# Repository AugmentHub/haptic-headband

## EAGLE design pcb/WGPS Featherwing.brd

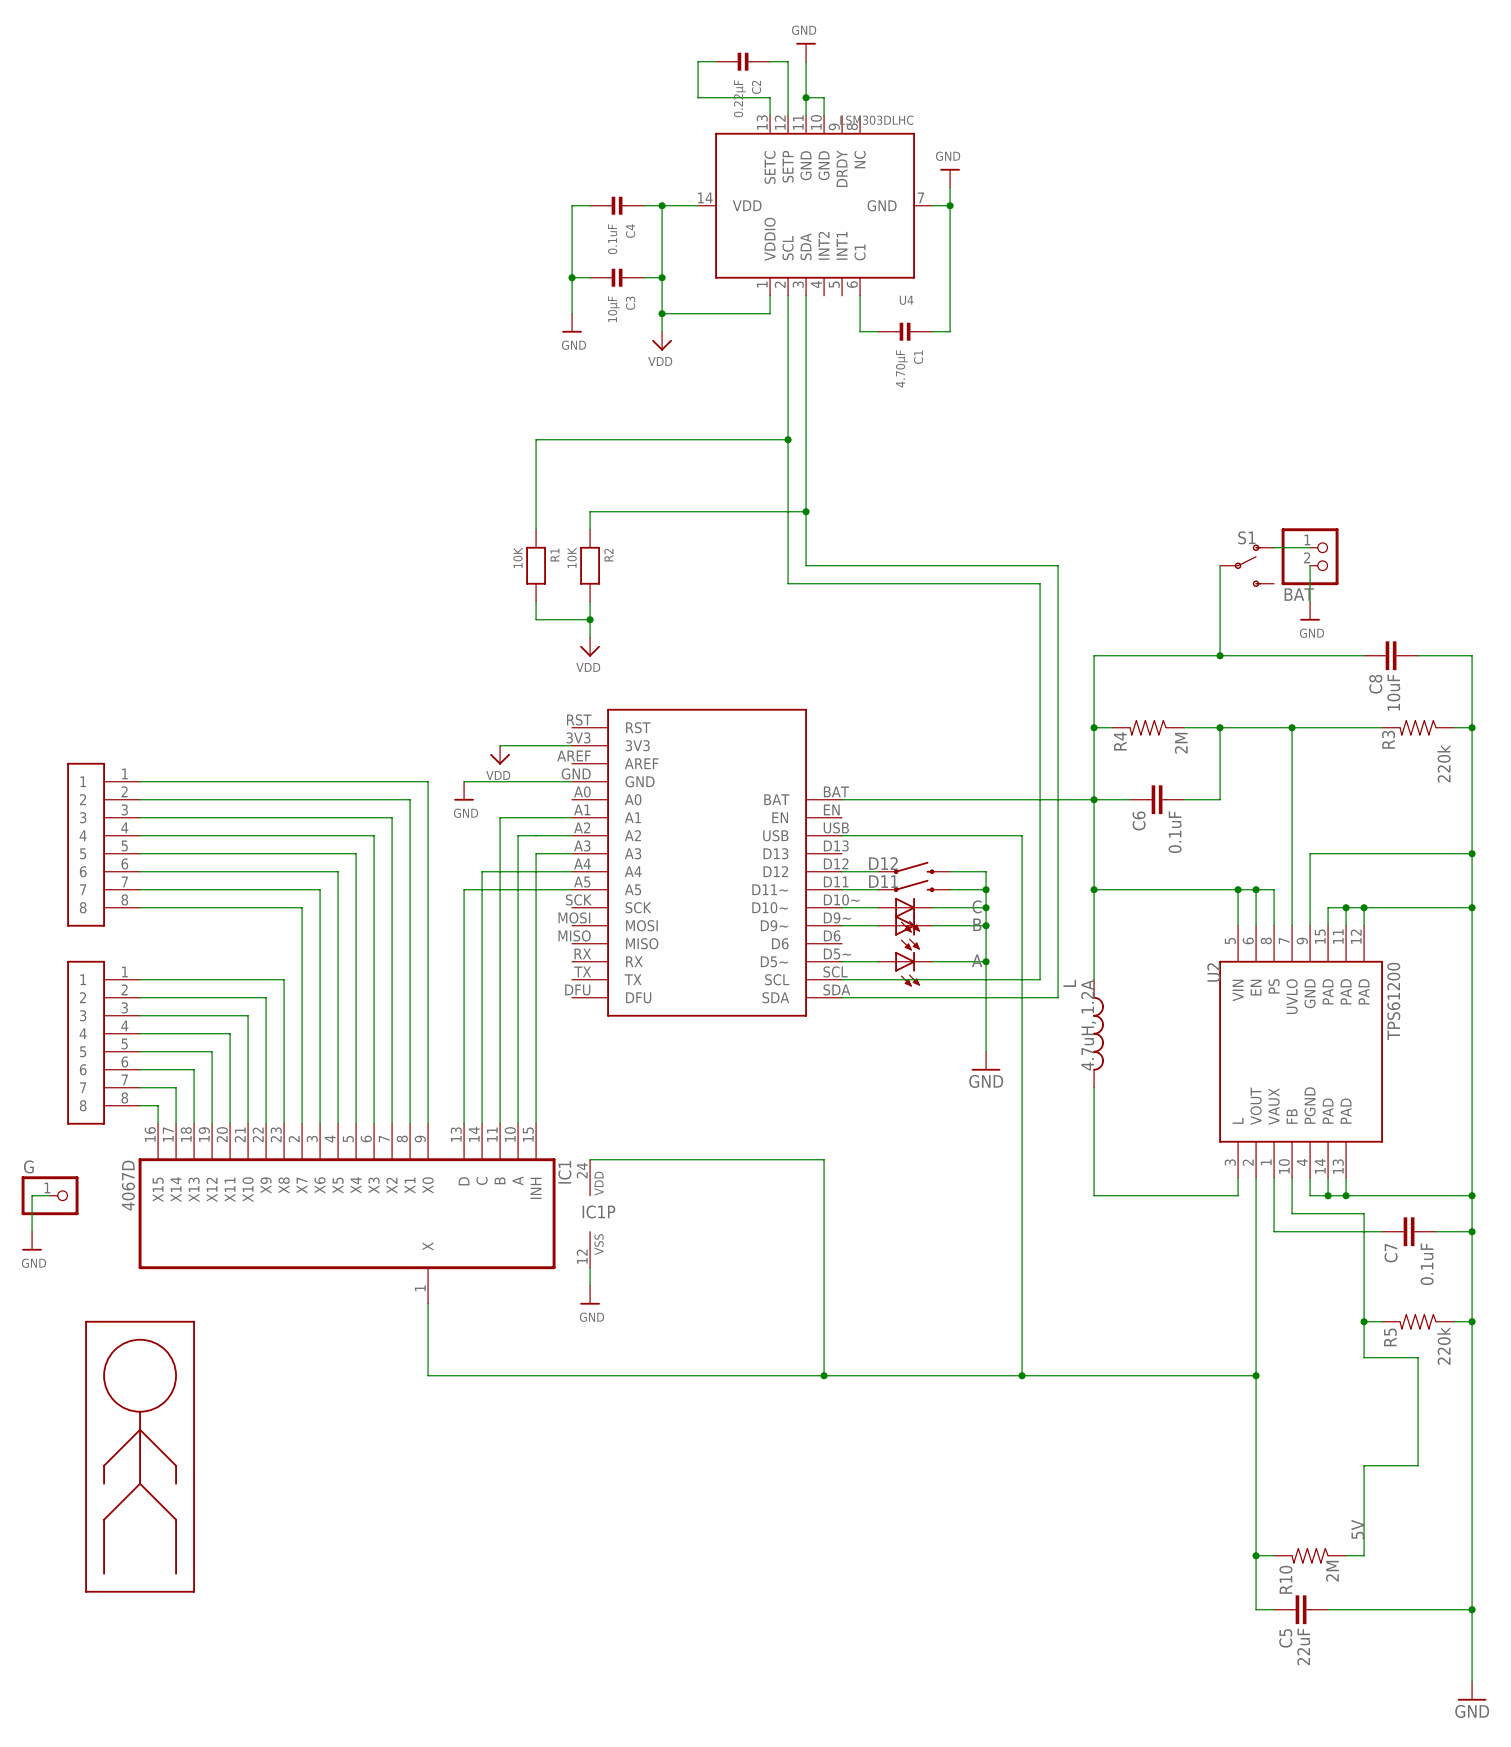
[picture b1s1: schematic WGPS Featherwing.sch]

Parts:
A: LEDCHIP-LED0805; CHIP-LED0805
B: LEDCHIP-LED0805; CHIP-LED0805
BAT: JST_2PIN-SMT-RA; JST-PH-2-SMT-RA
C: LEDCHIP-LED0805; CHIP-LED0805
C1: 4.70µF; _0805
C2: 0.22µF; _0805
C3: 10µF; _0805
C4: 0.1uF; _0805
C5: 22uF; 0805
C6, C7: 0.1uF; 0603-CAP
C8: 10uF; 1206
D11, D12: MOMENTARY-SWITCH-SPST-SMD-6.0X3.5MM; TACTILE_SWITCH_SMD_6.0X3.5MM
G: PINHD-1X1CB; 1X01-CLEANBIG
IC1: 4067D; SO24W
L: 4.7uH, 1.2A; CDRH2D09
R1, R2: 10K; _0805
R3, R5: 220k; 0603-RES
R4, R10: 2M; 0603-RES
S1: SWITCH-SPDT-SMD-RIGHT-ANGLE; SWITCH_SPST_SMD_A
U2: TPS61200; QFN-10_PAD
U4: LSM303DLHC; LGA14
U$1: SMD_FEATHERWING_BLE_32U4; FEATHERWING_MALE_SMD_HEADERS_0.1
U$6, U$7: SMD_JST_1X8
U$16: MAN_LOGO; MAN_LOGO_0.6

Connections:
5V: R5.2, R10.1, U2.10 (FB)
5V+: C5.1, IC1.1 (X), IC1.24 (VDD), R10.2, U2.2 (VOUT), U$1.USB
BAT: C6.1, C8.1, L.P$2 (2), R4.2, S1.2, U2.5 (VIN), U2.6 (EN), U2.8 (PS), U$1.BAT
C1: C1.2, U4.6 (C1)
C2.A: C2.1, U4.12 (SETP)
C2.B: C2.2, U4.13 (SETC)
GND: A.C, B.C, BAT.2 (1), C.C, C1.1, C3.2, C4.2, C5.2, C7.2, C8.2, D11.2, D12.2, G.1, IC1.12 (VSS), R3.1, R5.1, U2.4 (PGND), U2.9 (GND), U2.11 (PAD), U2.12 (PAD), U2.13 (PAD), U2.14 (PAD), U2.15 (PAD), U4.7 (GND), U4.10 (GND), U4.11 (GND), U$1.GND
L: L.P$1 (1), U2.3 (L)
MUX.0: IC1.9 (X0), U$6.1
MUX.1: IC1.8 (X1), U$6.2
MUX.2: IC1.7 (X2), U$6.3
MUX.3: IC1.6 (X3), U$6.4
MUX.4: IC1.5 (X4), U$6.5
MUX.5: IC1.4 (X5), U$6.6
MUX.6: IC1.3 (X6), U$6.7
MUX.7: IC1.2 (X7), U$6.8
MUX.8: IC1.23 (X8), U$7.1
MUX.9: IC1.22 (X9), U$7.2
MUX.10: IC1.21 (X10), U$7.3
MUX.11: IC1.20 (X11), U$7.4
MUX.12: IC1.19 (X12), U$7.5
MUX.13: IC1.18 (X13), U$7.6
MUX.14: IC1.17 (X14), U$7.7
MUX.15: IC1.16 (X15), U$7.8
MUX.A: IC1.10 (A), U$1.A2
MUX.B: IC1.11 (B), U$1.A1
MUX.C: IC1.14 (C), U$1.A4
MUX.D: IC1.13 (D), U$1.A5
MUX.INH: IC1.15 (INH), U$1.A3
unnamed: D11.1, U$1.D11 (D11~)
unnamed: BAT.1 (2), S1.1 (O)
unnamed: D12.1, U$1.D12
unnamed: A.A, U$1.D5~
unnamed: B.A, U$1.D9~
unnamed: C.A, U$1.D10~
unnamed: C7.1, U2.1 (VAUX)
SCL: R1.1, U4.2 (SCL), U$1.SCL
SDA: R2.1, U4.3 (SDA), U$1.SDA
UVLO1: C6.2, R3.2, R4.1, U2.7 (UVLO)
VDD: C3.1, C4.1, R1.2, R2.2, U4.1 (VDDIO), U4.14 (VDD), U$1.3V3

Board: 2 copper layers, 30 parts (14 on the bottom side), 40 nets, no tracks yet.

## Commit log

2024-08-15 updates to denim3

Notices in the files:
parts and their libraries:
microbuilder: This work is placed in the public domain, and may be freely used for commercial and non-commercial work with the following conditions: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
SparkFun-Switches: Licensing: Creative Commons ShareAlike 4.0 International - https://creativecommons.org/licenses/by-sa/4.0
